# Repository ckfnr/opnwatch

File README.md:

# opnwatch

**opnwatch** is an open-source wristwatch based on the ATmega328P microcontroller.

### Revision 2 of the PCB

### Revision 1 of the PCB

## Hardware

| Component | Part |
|-----------|------|
| Microcontroller | ATmega328P |
| Display | SSD1306 OLED |
| RTC | DS3231M |
| Charging IC | BQ24075RGT |
| PCB | Custom, designed in KiCad |

## Repository Structure

```
opnwatch/
├── CAD_files/        # KiCad schematic and PCB layout
    ├── rev2                # Revision 2 of the PCB
    └── rev3                # Revision 3 of the PCB
├── img/              # PCB and design images
└── watch_firmware/   # AVR-GCC firmware
    └── lib/
        └── oled-display/   # Vendored OLED library
```

## License

This project is open source. See [LICENSE](LICENSE) for details.

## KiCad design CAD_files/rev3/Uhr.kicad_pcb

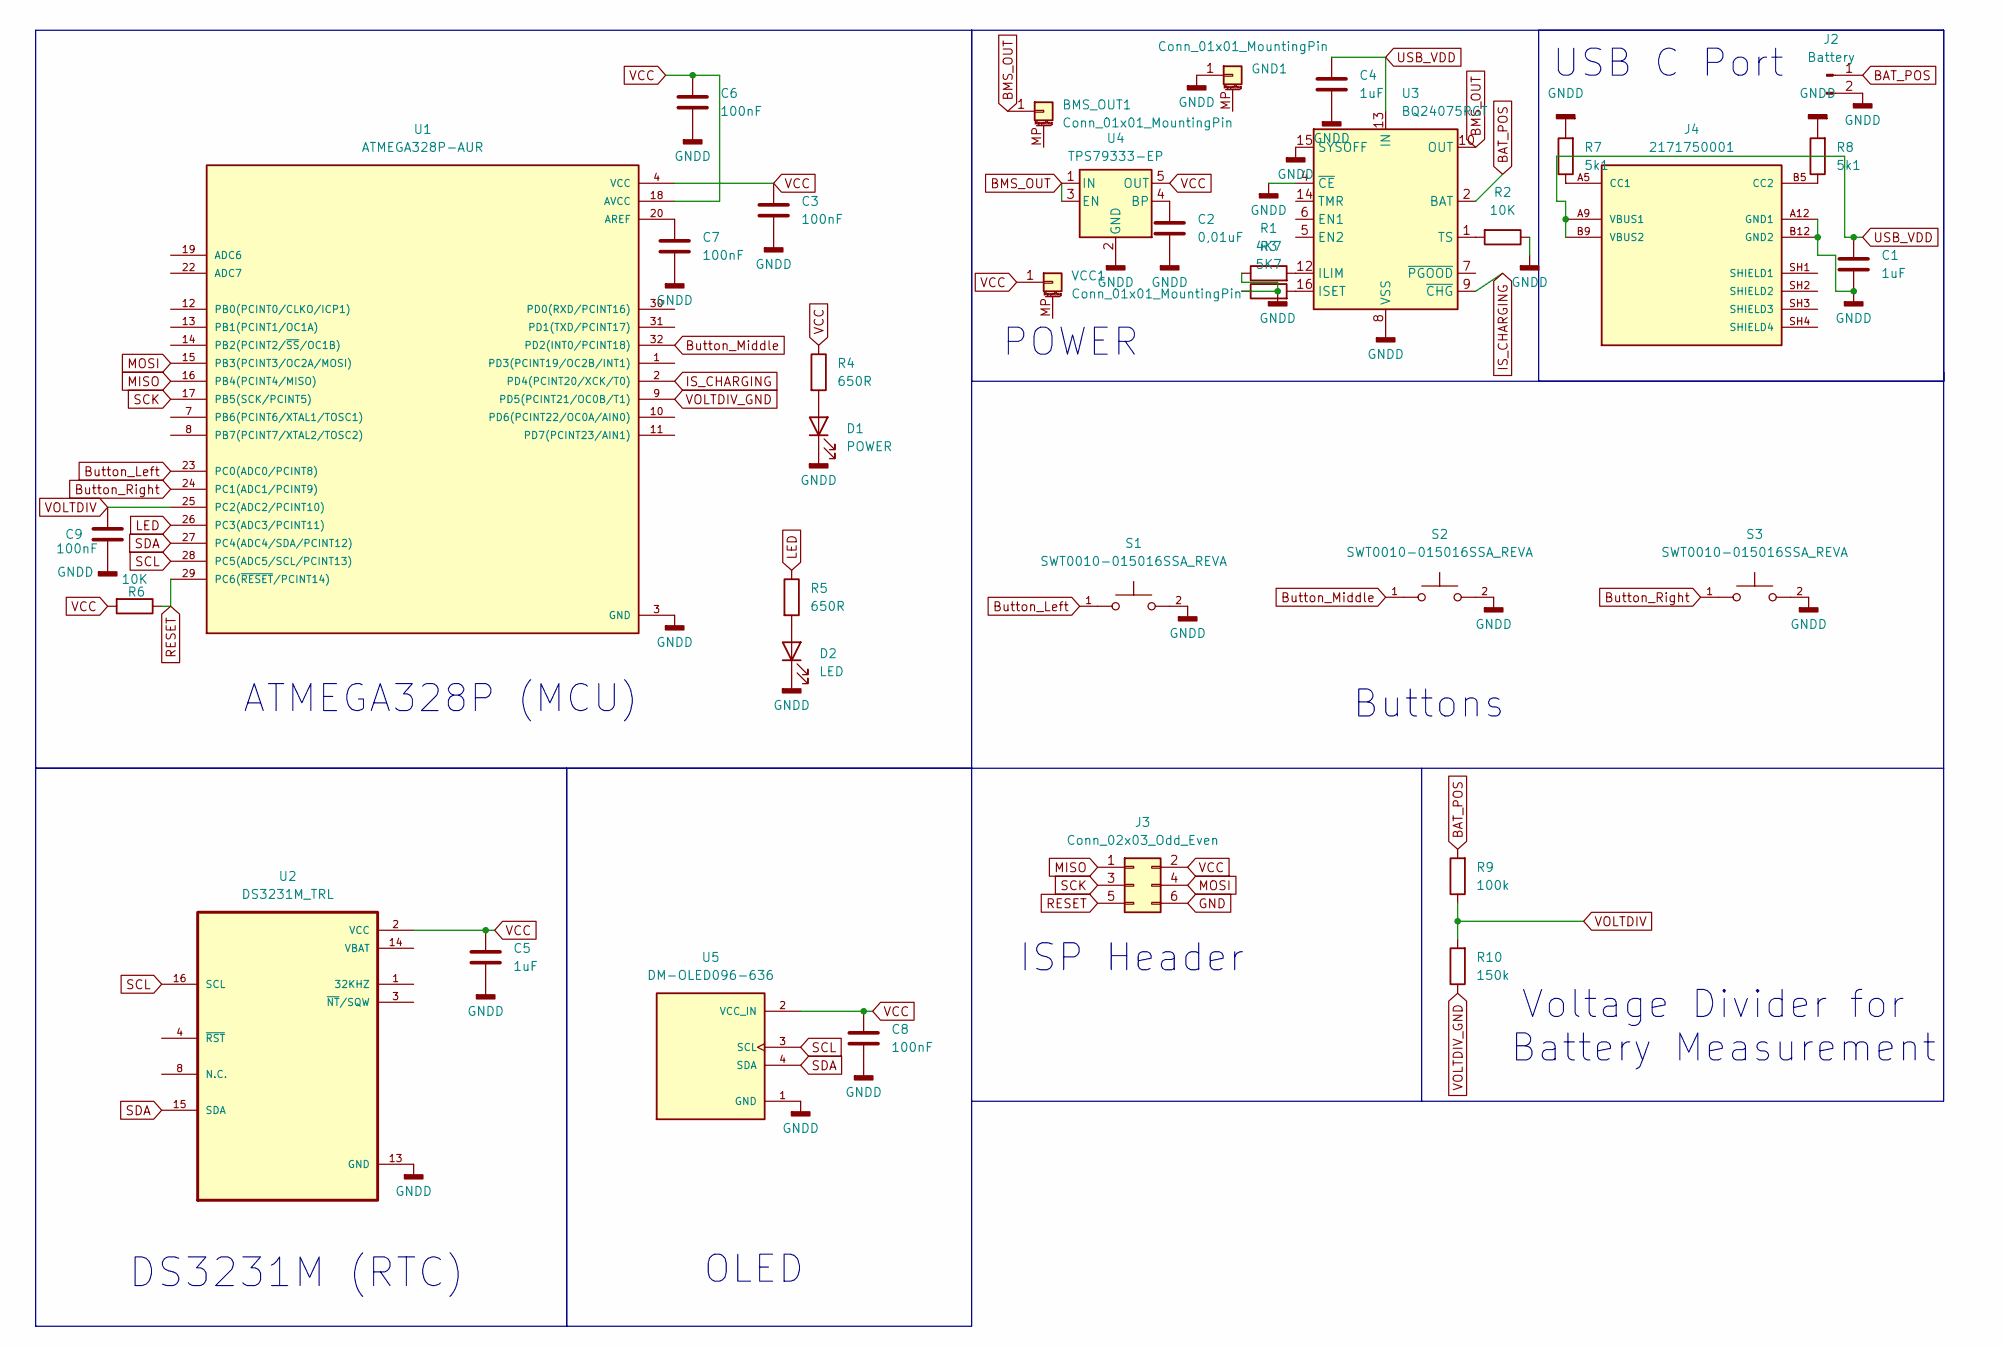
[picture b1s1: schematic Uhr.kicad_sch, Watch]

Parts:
BMS_OUT1: Conn_01x01_MountingPin; TestPoint_Pad_D1.5mm
C1, C4, C5: 1uF; C_0603_1608Metric
C2: 0,01uF; C_0603_1608Metric
C3: 100nF; C_0603_1608Metric_Pad1.08x0.95mm_HandSolder
C6, C7, C8, C9: 100nF; C_0603_1608Metric
D1: POWER; LED_0603_1608Metric
D2: LED; LED_0603_1608Metric
GND1: Conn_01x01_MountingPin; TestPoint_Pad_D1.5mm
J2: Battery; Wuerth_WR-WTB_64800211622_1x02_P1.50mm_Vertical
J3: Conn_02x03_Odd_Even; PinHeader_2x03_P1.00mm_Vertical
J4: 2171750001; MOLEX_2171750001; PARTREV A1
R1: 4K7; R_0603_1608Metric
R2, R6: 10K; R_0603_1608Metric
R3: 5K7; R_0603_1608Metric
R4, R5: 650R; R_0603_1608Metric
R7, R8: 5k1; R_0603_1608Metric
R9: 100k; R_0603_1608Metric
R10: 150k; R_0603_1608Metric
S1, S2, S3: SWT0010-015016SSA_REVA; SW_SWT0010-015016SSA_REVA; PARTREV A
U1: ATMEGA328P-AUR; QFP80P900X900X120-32N; PARTREV A
U2: DS3231M_TRL; SOIC127P1032X265-16N
U3: BQ24075RGT; VQFN-16-1EP_3x3mm_P0.5mm_EP1.6x1.6mm
U4: TPS79333-EP; SOT-23-5
U5: DM-OLED096-636; MODULE_DM-OLED096-636; PARTREV 2018-09-10
VCC1: Conn_01x01_MountingPin; TestPoint_Pad_D1.5mm

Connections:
BAT_POS: J2.1, R9.2, U3.2 (BAT), U3.3 (BAT)
BMS_OUT: BMS_OUT1.1 (Pin_1_1), U3.10 (OUT), U3.11 (OUT), U4.1 (IN), U4.3 (EN)
Button_Left: S1.1, U1.23 (PC0(ADC0/PCINT8))
Button_Middle: S2.1, U1.32 (PD2(INT0/PCINT18))
Button_Right: S3.1, U1.24 (PC1(ADC1/PCINT9))
IS_CHARGING: U1.2 (PD4(PCINT20/XCK/T0)), U3.9 (~CHG)
LED: R5.1, U1.26 (PC3(ADC3/PCINT11))
MISO: J3.1, U1.16 (PB4(PCINT4/MISO))
MOSI: J3.4, U1.15 (PB3(PCINT3/OC2A/MOSI))
unnamed: D1.2 (A), R4.2
unnamed: D2.2 (A), R5.2
unnamed: J4.A5 (CC1), R7.1
unnamed: J4.B5 (CC2), R8.1
unnamed: C7.1, U1.20 (AREF)
unnamed: U2.5 (N.C.), U2.6 (N.C.), U2.7 (N.C.), U2.8 (N.C.), U2.9 (N.C.), U2.10 (N.C.), U2.11 (N.C.), U2.12 (N.C.)
unnamed: R1.2, U3.12 (ILIM)
unnamed: R3.2, U3.16 (ISET)
unnamed: R2.2, U3.1 (TS)
unnamed: C2.1, U4.4 (BP)
RESET: J3.5, R6.1, U1.29 (PC6(~RESET/PCINT14))
SCK: J3.3, U1.17 (PB5(SCK/PCINT5))
SCL: U1.28 (PC5(ADC5/SCL/PCINT13)), U2.16 (SCL), U5.3 (SCL)
SDA: U1.27 (PC4(ADC4/SDA/PCINT12)), U2.15 (SDA), U5.4 (SDA)
USB_VDD: C1.1, C4.1, J4.A9 (VBUS1), J4.B9 (VBUS2), U3.13 (IN)
VCC: C3.2, C5.1, C6.1, C8.1, J3.2, R4.1, R6.2, U1.4 (VCC), U1.6 (VCC), U1.18 (AVCC), U2.2 (VCC), U4.5 (OUT), U5.2 (VCC_IN), VCC1.1 (Pin_1_1)
VOLTDIV: C9.1, R9.1, R10.2, U1.25 (PC2(ADC2/PCINT10))
VOLTDIV_GND: R10.1, U1.9 (PD5(PCINT21/OC0B/T1))

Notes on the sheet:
Buttons
Voltage Divider for Battery Measurement
USB C Port
POWER
OLED
ISP Header
ATMEGA328P (MCU)
DS3231M (RTC)

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
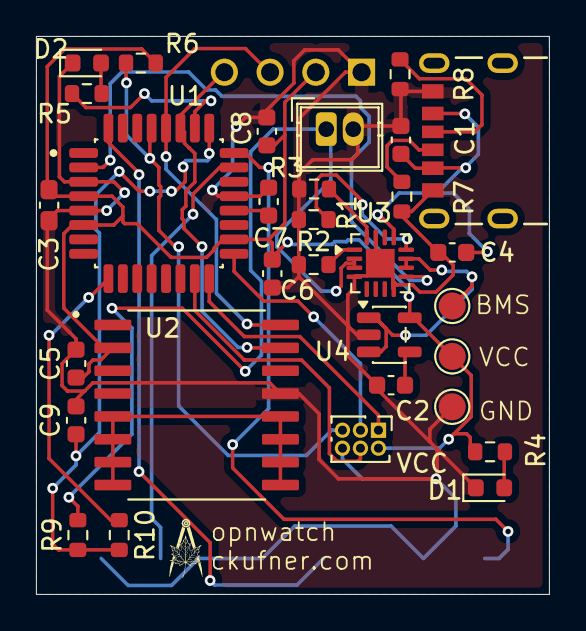
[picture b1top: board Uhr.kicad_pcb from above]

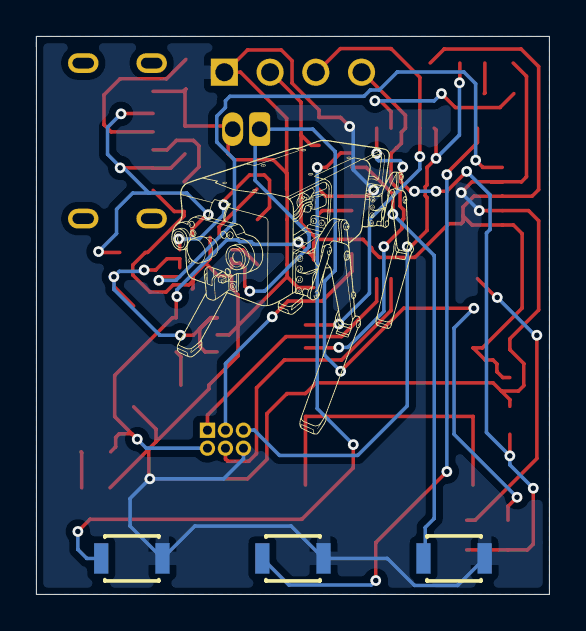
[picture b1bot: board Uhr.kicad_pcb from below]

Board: 2 copper layers, 28.5 x 31.0 mm, 35 parts (4 on the bottom side), 28 nets.

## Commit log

2026-05-13 add oled-display lib as vendor dependency
2026-05-13 ignore KiCad history directory
2026-05-13 ignore build artifacts
2026-05-13 ignore build directory
2026-05-13 vendor oled-display lib properly
2026-05-13 Add GNU General Public License version 3
2026-05-13 added readme
2026-05-13 added images
2026-05-14 revision 3 of the PCB
2026-05-14 updated readme, removed backups from CAD folders
2026-05-15 removed leftover traces from rev2
